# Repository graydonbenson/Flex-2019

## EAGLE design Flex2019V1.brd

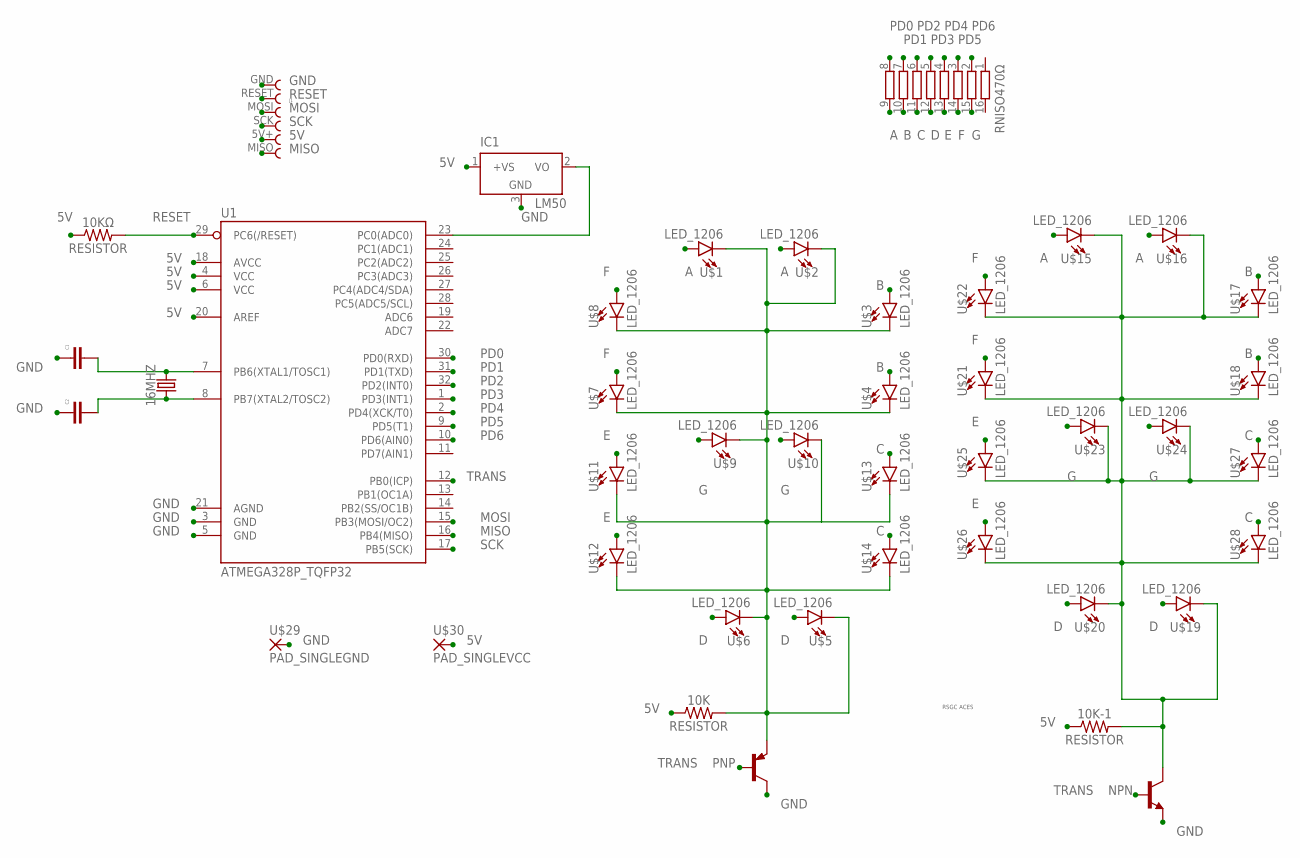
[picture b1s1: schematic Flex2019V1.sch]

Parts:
10K, 10K-1, 10KΩ: RESISTOR; R1206
16MHZ: CRYSTALSMD-5X3.2-2PAD; CRYSTAL-SMD-5X3.2-2PAD
C1, C2: CAPACITOR_1206_NONPPOLAR; C1206
IC1: LM50; SOT23
J1: CONN_FPC_ISPCONNECTOR_PADS; 68610614122
NPN: -NPN-SOT23-BEC; SOT23-BEC
PNP: -PNP-SOT23-BEC; SOT23-BEC
RNISO470Ω: RESISTOR_NETWORK; 4816P
U1: ATMEGA328P_TQFP32; TQFP32-08
U$1, U$2, U$3, U$4, U$5, U$6, U$7, U$8, U$9, U$10, U$11, U$12, U$13, U$14, U$15, U$16, U$17, U$18, U$19, U$20, U$21, U$22, U$23, U$24, U$25, U$26, U$27, U$28: LED_1206; CHIPLED_1206
U$29: PAD_SINGLEGND; PAD_GND
U$30: PAD_SINGLEVCC; PAD_VCC
U$31: ACES_LOGO

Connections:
5V: 10K.1, 10K-1.1, 10KΩ.1, IC1.1 (+VS), J1.5V+, U1.4 (VCC), U1.6 (VCC), U1.18 (AVCC), U1.20 (AREF), U$30.1
A: RNISO470Ω.9, U$1.A, U$2.A, U$15.A, U$16.A
B: RNISO470Ω.10, U$3.A, U$4.A, U$17.A, U$18.A
C: RNISO470Ω.11, U$13.A, U$14.A, U$27.A, U$28.A
D: RNISO470Ω.12, U$5.A, U$6.A, U$19.A, U$20.A
E: RNISO470Ω.13, U$11.A, U$12.A, U$25.A, U$26.A
F: RNISO470Ω.14, U$7.A, U$8.A, U$21.A, U$22.A
G: RNISO470Ω.15, U$9.A, U$10.A, U$23.A, U$24.A
GND: C1.1, C2.1, IC1.3 (GND), J1.GND, NPN.E, PNP.C, U1.3 (GND), U1.5 (GND), U1.21 (AGND), U$29.1
MISO: J1.MISO, U1.16 (PB4(MISO))
MOSI: J1.MOSI, U1.15 (PB3(MOSI/OC2))
unnamed: IC1.2 (VO), U1.23 (PC0(ADC0))
unnamed: 16MHZ.P$2 (2), C1.2, U1.7 (PB6(XTAL1/TOSC1))
unnamed: 16MHZ.P$1 (1), C2.2, U1.8 (PB7(XTAL2/TOSC2))
unnamed: 10K.2, PNP.E, U$1.C, U$2.C, U$3.C, U$4.C, U$5.C, U$6.C, U$7.C, U$8.C, U$9.C, U$10.C, U$11.C, U$12.C, U$13.C, U$14.C
unnamed: 10K-1.2, NPN.C, U$15.C, U$16.C, U$17.C, U$18.C, U$19.C, U$20.C, U$21.C, U$22.C, U$23.C, U$24.C, U$25.C, U$26.C, U$27.C, U$28.C
PD0: RNISO470Ω.8, U1.30 (PD0(RXD))
PD1: RNISO470Ω.7, U1.31 (PD1(TXD))
PD2: RNISO470Ω.6, U1.32 (PD2(INT0))
PD3: RNISO470Ω.5, U1.1 (PD3(INT1))
PD4: RNISO470Ω.4, U1.2 (PD4(XCK/T0))
PD5: RNISO470Ω.3, U1.9 (PD5(T1))
PD6: RNISO470Ω.2, U1.10 (PD6(AIN0))
RESET: 10KΩ.2, J1.RESET, U1.29 (PC6(/RESET))
SCK: J1.SCK, U1.17 (PB5(SCK))
TRANS: NPN.B, PNP.B, U1.12 (PB0(ICP))

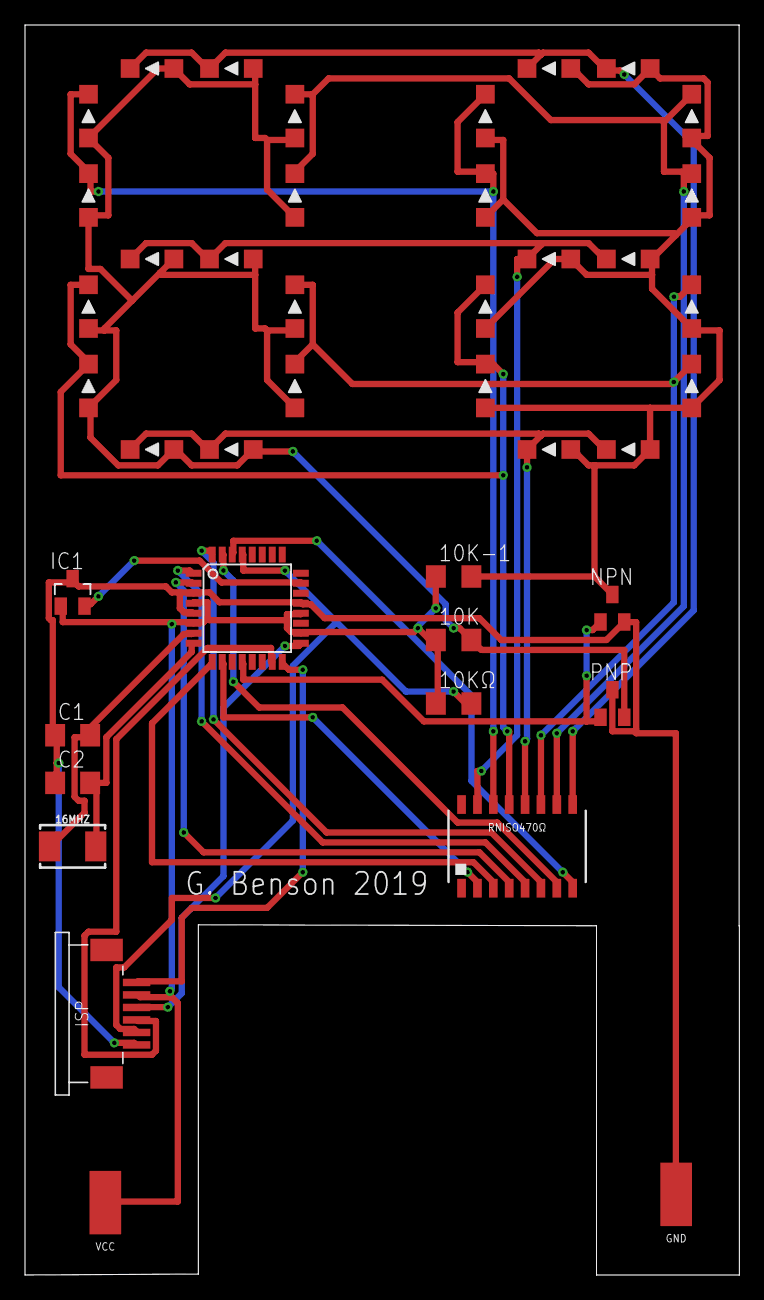
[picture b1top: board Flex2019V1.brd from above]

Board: 2 copper layers, 57.1 x 100.0 mm, 43 parts (0 on the bottom side), 26 nets.

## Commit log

2019-05-02 Add files via upload
    Use this CAM file for board processing.

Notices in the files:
parts and their libraries:
SparkFun-Clocks: Licensing: Creative Commons ShareAlike 4.0 International - https://creativecommons.org/licenses/by-sa/4.0
